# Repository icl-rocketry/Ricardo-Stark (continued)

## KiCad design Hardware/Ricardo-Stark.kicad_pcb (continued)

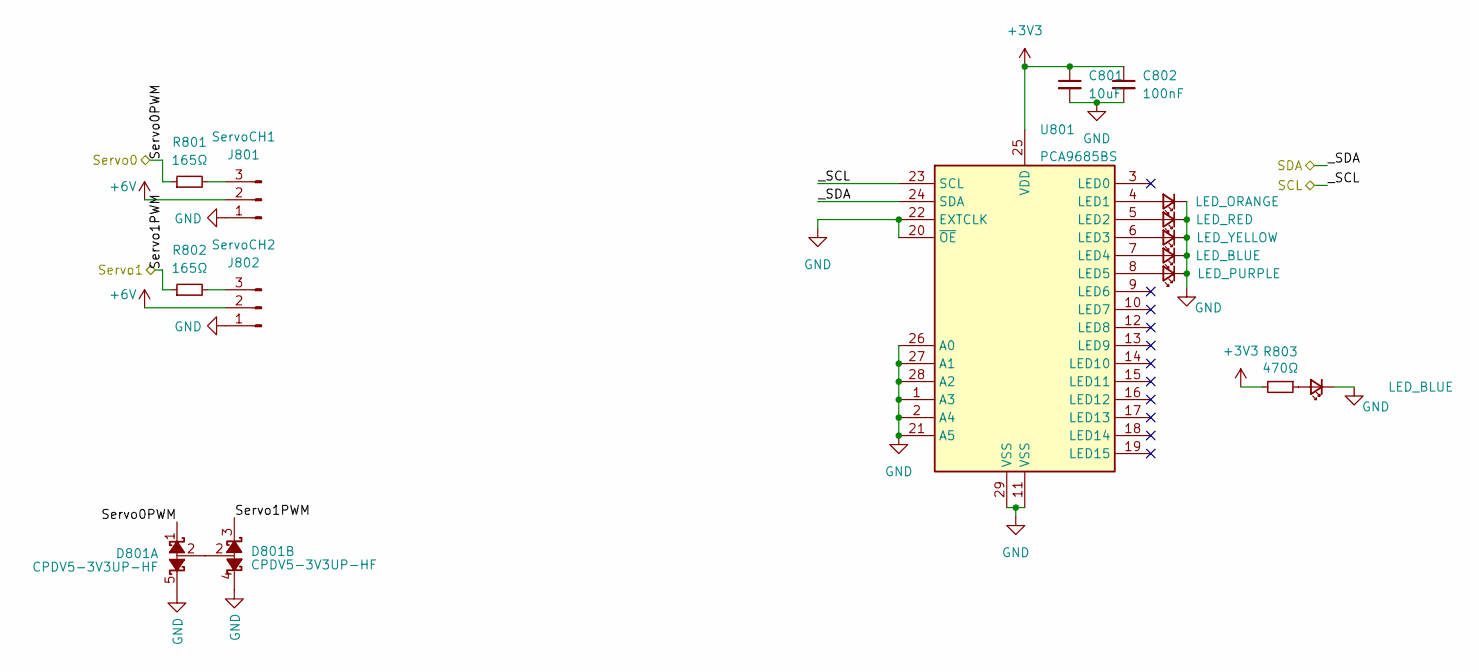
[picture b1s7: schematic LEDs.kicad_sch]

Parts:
C801: 10uF; C_0402_1005Metric
C802: 100nF; C_0402_1005Metric
D801: CPDV5-3V3UP-HF; SOT-353_SC-70-5
D802: LED_ORANGE; LED_0402_1005Metric
D803: LED_RED; LED_0402_1005Metric
D804: LED_YELLOW; LED_0402_1005Metric
D805, D807: LED_BLUE; LED_0402_1005Metric
D806: LED_PURPLE; LED_0402_1005Metric
J801: ServoCH1; Molex_Nano-Fit_105313-xx03_1x03_P2.50mm_Horizontal
J802: ServoCH2; Molex_Nano-Fit_105313-xx03_1x03_P2.50mm_Horizontal
R801, R802: 165Ω; R_0402_1005Metric
R803: 470Ω; R_0402_1005Metric
U801: PCA9685BS; QFN-28-1EP_6x6mm_P0.65mm_EP4.25x4.25mm

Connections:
+3.3V: C801.1, C802.1, R803.2, U801.25 (VDD); also elsewhere on the board
+6V: J801.2, J802.2; also elsewhere on the board
/SCL: U801.23 (SCL); also elsewhere on the board
/SDA: U801.24 (SDA); also elsewhere on the board
/Servo0: D801.1, R801.1; also elsewhere on the board
/Servo1: D801.3, R802.1; also elsewhere on the board
GND: C801.2, C802.2, D801.4, D801.5, D802.1 (K), D803.1 (K), D804.1 (K), D805.1 (K), D806.1 (K), D807.1 (K), J801.1, J802.1, U801.1 (A3), U801.2 (A4), U801.11 (VSS), U801.20 (~OE), U801.21 (A5), U801.22 (EXTCLK), U801.26 (A0), U801.27 (A1), U801.28 (A2), U801.29 (VSS); also elsewhere on the board
unnamed: D802.2 (A), U801.4 (LED1)
unnamed: D803.2 (A), U801.5 (LED2)
unnamed: D804.2 (A), U801.6 (LED3)
unnamed: D805.2 (A), U801.7 (LED4)
unnamed: D806.2 (A), U801.8 (LED5)
unnamed: D807.2 (A), R803.1
unnamed: J801.3, R801.2
unnamed: J802.3, R802.2

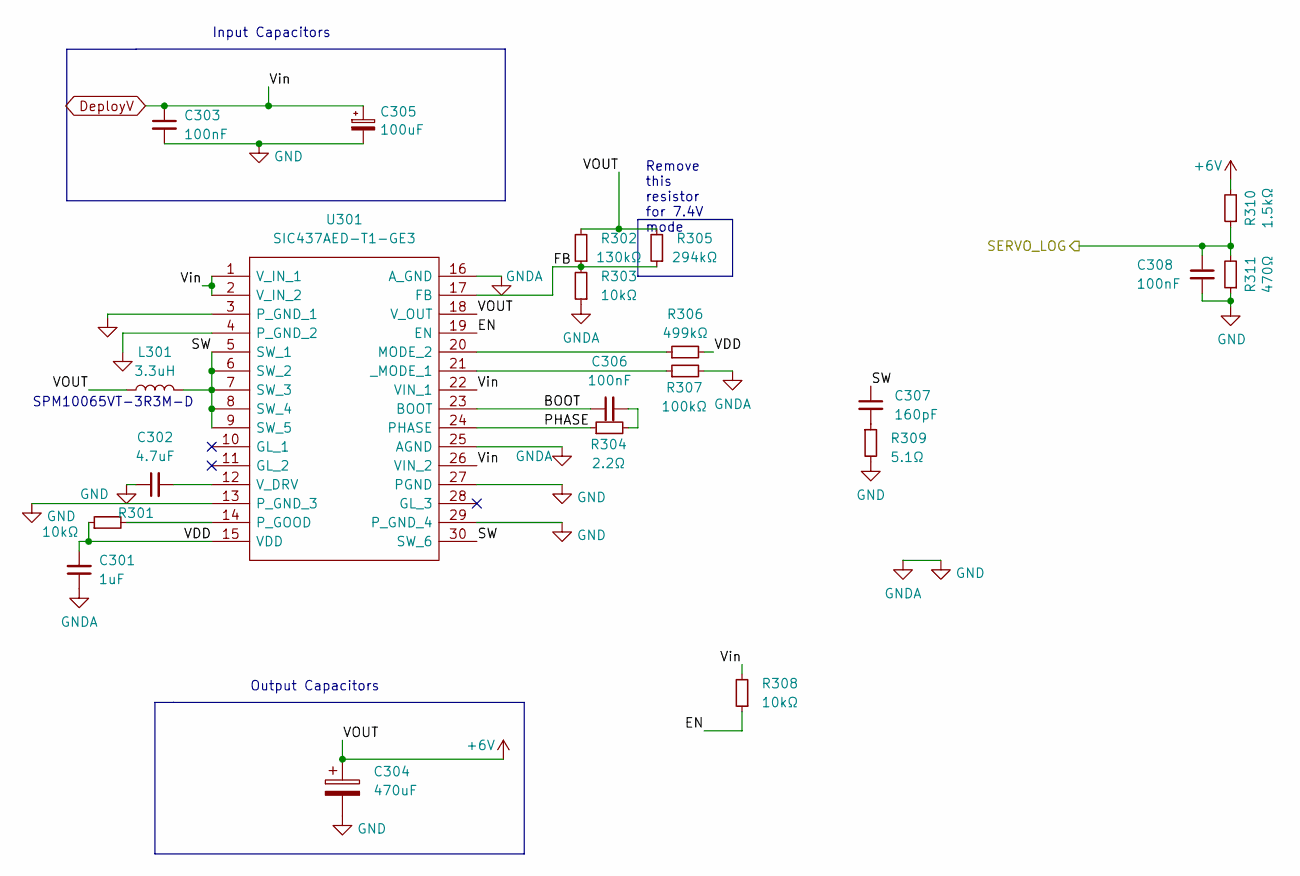
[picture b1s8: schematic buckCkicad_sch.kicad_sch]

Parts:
C301: 1uF; C_0402_1005Metric
C302: 4.7uF; C_0402_1005Metric
C303, C306, C308: 100nF; C_0402_1005Metric
C304: 470uF; CP_Elec_6.3x7.7
C305: 100uF; CP_EIA-7360-38_Kemet-E
C307: 160pF; C_0603_1608Metric
L301: 3.3uH; IND_SPM10065VT-3R3M-D
R301, R303, R308: 10kΩ; R_0402_1005Metric
R302: 130kΩ; R_0402_1005Metric
R304: 2.2Ω; R_0402_1005Metric
R305: 294kΩ; R_0603_1608Metric_Pad0.98x0.95mm_HandSolder
R306: 499kΩ; R_0402_1005Metric
R307: 100kΩ; R_0402_1005Metric
R309: 5.1Ω; R_0603_1608Metric
R310: 1.5kΩ; R_0402_1005Metric
R311: 470Ω; R_0402_1005Metric
U301: SIC437AED-T1-GE3; SiC437BEDT1GE3; Manufacturer_Part_Number SiC437BED-T1-GE3; Mouser Part Number 78-SIC437BED-T1-GE3

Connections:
+6V: C304.1, L301.1, R302.2, R305.2, R310.2, U301.18 (V_OUT); also elsewhere on the board
/ServoPower/BOOT: C306.1, U301.23 (BOOT)
/ServoPower/EN: R308.1, U301.19 (EN)
/ServoPower/FB: R302.1, R303.2, R305.1, U301.17 (FB)
/ServoPower/PHASE: R304.1, U301.24 (PHASE)
/ServoPower/SW: C307.1, L301.2, U301.5 (SW_1), U301.6 (SW_2), U301.7 (SW_3), U301.8 (SW_4), U301.9 (SW_5), U301.30 (SW_6)
/ServoPower/VDD: C301.2, R301.1, R306.2, U301.15 (VDD)
/ServoV_LOG: C308.1, R310.1, R311.2; also elsewhere on the board
DeployV: C303.1, C305.1, R308.2, U301.1 (V_IN_1), U301.2 (V_IN_2), U301.22 (VIN_1), U301.26 (VIN_2); also elsewhere on the board
GND: C301.1, C302.1, C303.2, C304.2, C305.2, C308.2, R303.1, R307.2, R309.2, R311.1, U301.3 (P_GND_1), U301.4 (P_GND_2), U301.13 (P_GND_3), U301.16 (A_GND), U301.25 (AGND), U301.27 (PGND), U301.29 (P_GND_4); also elsewhere on the board
unnamed: C306.2, R304.2
unnamed: C307.2, R309.1
unnamed: R306.1, U301.20 (MODE_2)
unnamed: R301.2, U301.14 (P_GOOD)
unnamed: C302.2, U301.12 (V_DRV)
unnamed: R307.1, U301.21 (_MODE_1)

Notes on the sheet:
SPM10065VT-3R3M-D
Input Capacitors
Output Capacitors
Remove this resistor for 7.4V mode

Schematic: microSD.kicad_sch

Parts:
C1001: 100nF; C_0402_1005Metric
J1001: Conn_01x07_Socket; Molex_Pico-Clasp_202396-0707_1x07-1MP_P1.00mm_Horizontal
J1002: ST1W008S4TR2000; JAE_ST1W008S4TR2000; PARTREV 1
R1001, R1002: 10kΩ; R_0402_1005Metric

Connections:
+3.3V: C1001.1, J1001.7, J1002.C4, R1001.1, R1002.2; also elsewhere on the board
/SD1_CS: J1002.C2; also elsewhere on the board
/SD1_DET: J1002.SW, R1002.1; also elsewhere on the board
/SD2_CS: J1001.2; also elsewhere on the board
/SD2_DET: J1001.1, R1001.2; also elsewhere on the board
/VSPI_MISO: J1001.6, J1002.C7; also elsewhere on the board
/VSPI_MOSI: J1001.3, J1002.C3; also elsewhere on the board
/VSPI_SCLK: J1001.5, J1002.C5; also elsewhere on the board
GND: C1001.2, J1001.4, J1002.C6, J1002.GND1 (GND), J1002.GND2 (GND), J1002.GND3 (GND), J1002.GND4 (GND); also elsewhere on the board

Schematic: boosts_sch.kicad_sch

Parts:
C401, C422: 10uF; C_0402_1005Metric
C402, C409, C411, C420, C421, C423: 100nF; C_0402_1005Metric
C403: 2.2uF; C_0603_1608Metric
C404: 180pF; C_0402_1005Metric
C405: 3.9nF; C_0402_1005Metric
C406, C413: 1uF; C_0402_1005Metric
C407, C408, C417, C419: 22uF; C_0805_2012Metric
C410, C418: 2.2uF; C_0402_1005Metric
C412: 47uF; C_1206_3216Metric
C414: 10uF; C_0603_1608Metric
C415: 120pF; C_0402_1005Metric
C416: 2.2nF; C_0402_1005Metric
C424: 22uF; C_1206_3216Metric
L401, L402: 5uH; IND_SRP6540-390M; Manufacturer_Part_Number SRR6038-5R0Y; Mouser Part Number 652-SRR6038-5R0Y
R401: 7.87kΩ; R_0402_1005Metric
R402: 360kΩ; R_0402_1005Metric
R403, R411: 100kΩ; R_0402_1005Metric
R404, R414: 10kΩ; R_0402_1005Metric
R405: 560kΩ; R_0402_1005Metric
R406, R412: 49.9kΩ; R_0402_1005Metric
R407: 150kΩ; R_0402_1005Metric
R408: 301kΩ; R_0402_1005Metric
R409: 18.7kΩ; R_0402_1005Metric
R410: 976kΩ; R_0402_1005Metric
R413: 432kΩ; R_0402_1005Metric
R415: 475kΩ; R_0402_1005Metric
R416: 287kΩ; R_0402_1005Metric
U401, U404: TPS61089RNRR; IC_TPS61089RNRR; Manufacturer_Part_Number TPS61089RNRR; Mouser Part Number 595-TPS61089RNRR
U402, U403: AP2205-W5-7; SOT95P282X145-5N; Mouser Part Number 621-AP2205-W5-7

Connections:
+3.3V: C411.1, C412.1, C421.1, C424.1, L401.1, L402.1, R404.2, R414.2, U401.9 (VIN), U404.9 (VIN); also elsewhere on the board
+5V: C410.1, R407.2, U402.5 (VOUT); also elsewhere on the board
+12V: C418.1, R413.2, U403.5 (VOUT); also elsewhere on the board
/Boosts/FB_5V: R402.1, R403.2, U401.3 (FB)
/Boosts/FB_12V: R410.1, R411.2, U404.3 (FB)
/Boosts/LDO5.5V_IN: C401.1, C402.1, C406.1, C407.1, C408.1, R402.2, U401.6 (VOUT), U402.1 (VIN), U402.3 (EN)
/Boosts/LDO12V_IN: C413.1, C417.1, C419.1, C422.1, C423.1, R410.2, U403.1 (VIN), U403.3 (EN), U404.6 (VOUT)
/Boosts/SW_5V: R408.1, U401.1 (FSW)
/Boosts/SW_12V: R416.1, U404.1 (FSW)
GND: C401.2, C402.2, C403.2, C404.2, C405.2, C406.2, C407.2, C408.2, C410.2, C411.2, C412.2, C413.2, C414.2, C415.2, C416.2, C417.2, C418.2, C419.2, C421.2, C422.2, C423.2, C424.2, R403.1, R405.1, R406.1, R411.1, R412.1, R415.1, U401.5 (GND), U402.2 (GND), U403.2 (GND), U404.5 (GND); also elsewhere on the board
unnamed: C405.1, R401.2
unnamed: C416.1, R409.2
unnamed: C409.1, U401.10 (BOOT)
unnamed: C404.1, R401.1, U401.4 (COMP)
unnamed: R404.1, U401.7 (EN)
unnamed: R405.2, U401.8 (ILIM)
unnamed: C409.2, L401.2, R408.2, U401.11 (SW)
unnamed: C403.1, U401.2 (VCC)
unnamed: R406.2, R407.1, U402.4 (ADJ/NC)
unnamed: R412.2, R413.1, U403.4 (ADJ/NC)
unnamed: C420.1, U404.10 (BOOT)
unnamed: C415.1, R409.1, U404.4 (COMP)
unnamed: R414.1, U404.7 (EN)
unnamed: R415.2, U404.8 (ILIM)
unnamed: C420.2, L402.2, R416.2, U404.11 (SW)
unnamed: C414.1, U404.2 (VCC)

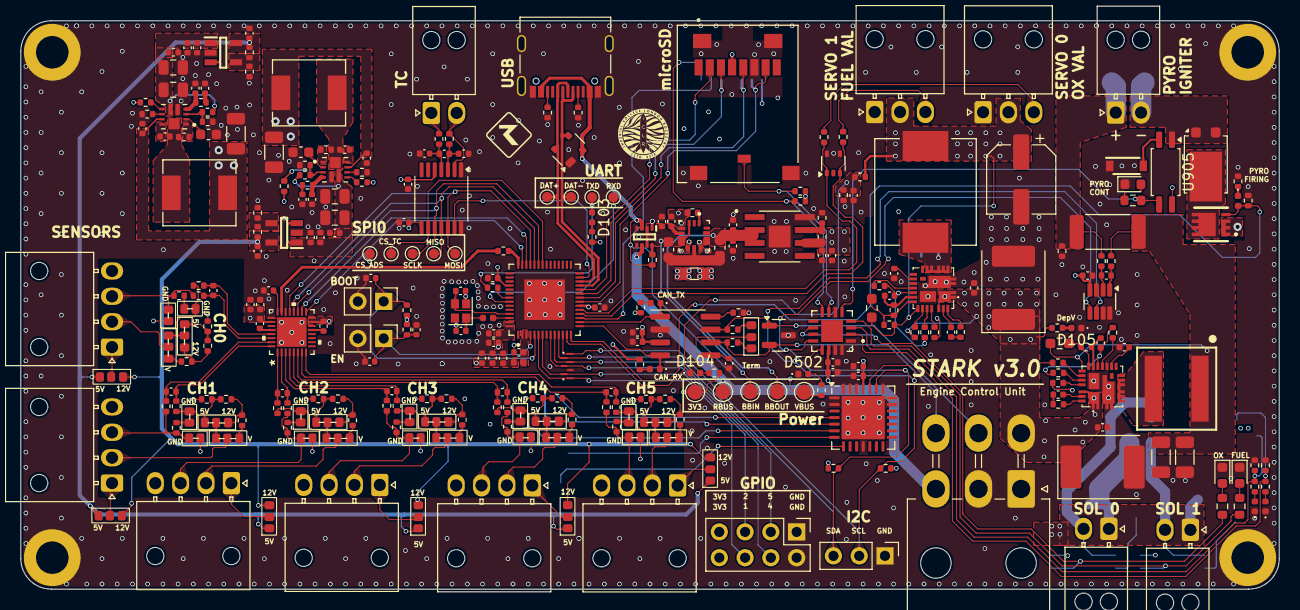
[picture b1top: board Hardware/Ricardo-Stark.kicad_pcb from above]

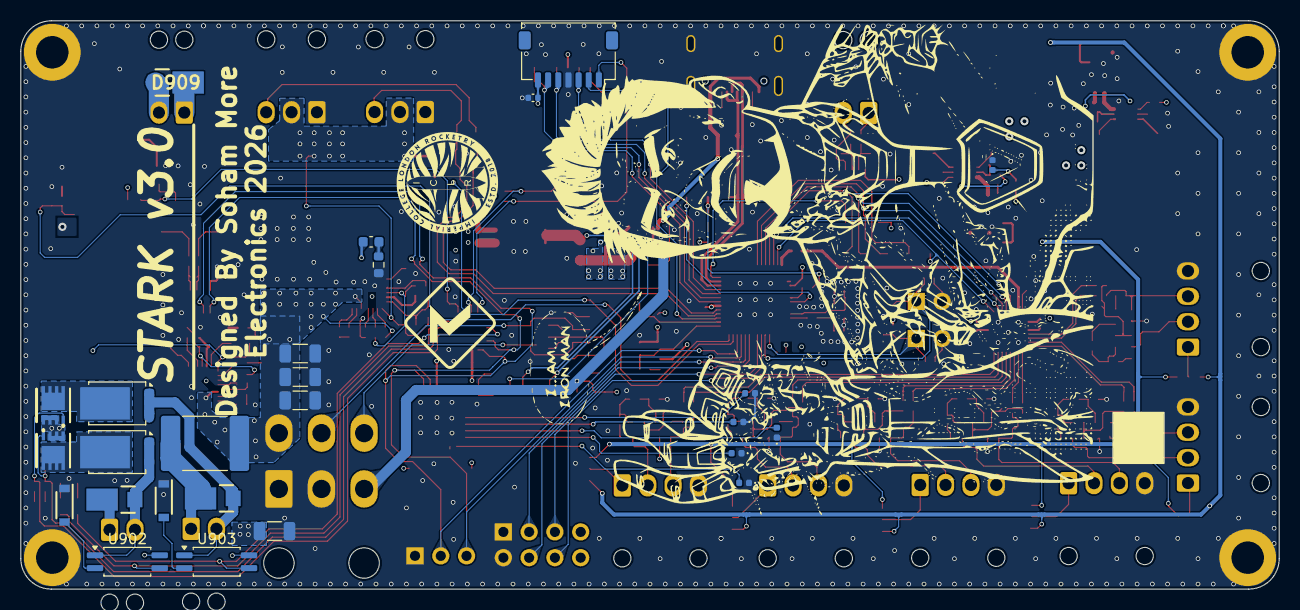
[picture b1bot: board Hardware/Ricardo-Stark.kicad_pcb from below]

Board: 4 copper layers, 124.0 x 56.0 mm, 332 parts (26 on the bottom side), 212 nets.

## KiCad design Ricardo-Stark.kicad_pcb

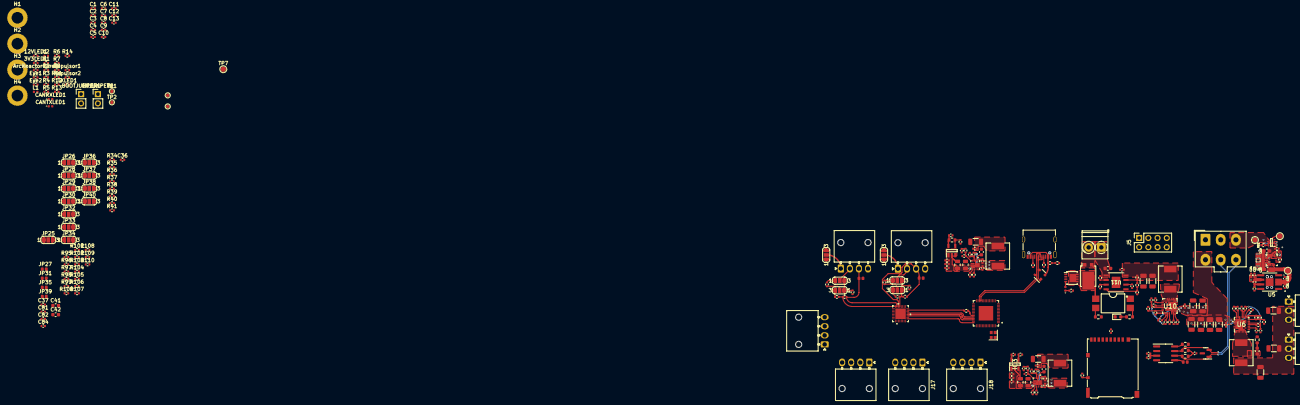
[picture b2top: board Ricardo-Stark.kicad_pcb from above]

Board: 4 copper layers, 265 parts (0 on the bottom side), 164 nets.

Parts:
3V3LED1: BLUE_LED; R_0402_1005Metric
12VLED1: RED_LED; R_0402_1005Metric
ArcReactorCore1: Blue_LED; R_0402_1005Metric
BOOTJUMPER1: Conn_01x02_Male; PinHeader_1x02_P2.54mm_Vertical
C1, C15, C17, C21, C23, C58, C68: 10uF; C_0402_1005Metric
C2, C4, C7, C19, C25, C37, C51, C60, C73, C82: 1uF; C_0402_1005Metric
C3, C5, C6, C8, C10, C11, C24, C35, C36, C76, C77, C84: 0.1uF; C_0402_1005Metric
C9: 10nF; C_0402_1005Metric
C12, C13: 11pF; C_0402_1005Metric
C14, C34, C54, C56, C59, C66, C67, C69, C83, C86: 100nF; C_0402_1005Metric
C16: 47nF; C_0402_1005Metric
C18, C41, C61: 10uF; C_0603_1608Metric
C20: 22uF; C_0603_1608Metric
C22, C26, C74: 4.7uF; C_0402_1005Metric
C27, C28, C40, C57, C75, C80, C85: 47uF; C_1206_3216Metric
C29: 68uF; C_1206_3216Metric
C30, C32: DNP; C_1206_3216Metric
C31, C33: 220uF; C_1206_3216Metric
C39, C52, C53, C64: 22uF; C_0805_2012Metric
C42: 100nF; C_0603_1608Metric
C48: 2.2uF; C_0603_1608Metric
C49: 180pF; C_0402_1005Metric
C50: 3.9nF; C_0402_1005Metric
C55, C65: 2.2uF; C_0402_1005Metric
C62: 120pF; C_0402_1005Metric
C63, C87: 2.2nF; C_0402_1005Metric
C70: 22uF; C_1206_3216Metric
C78: 680pF; C_0603_1608Metric
C81: 220nF; C_0402_1005Metric
C88: 1uF; C_0603_1608Metric
CANRXLED1: CANRXLED; LED_0402_1005Metric
CANTXLED1: CANTXLED; LED_0402_1005Metric
D1: SM712_SOT23; SOT-23
D2: SP0503BAHT; SOT-143
D3: DST1550S; TO-277B
D4: RED_LED; LED_0603_1608Metric
ENJUMPER1: Conn_01x02_Male; PinHeader_1x02_P2.54mm_Vertical
Eye1, Eye2: Blue_LED; R_0402_1005Metric
Firing1: EMERALD_LED; LED_0402_1005Metric
H1, H2, H3, H4: MountingHole_Pad; MountingHole_3.2mm_M3_DIN965_Pad
IC1, IC4: TPS61089RNRR; IC_TPS61089RNRR
IC2, IC3: AP2205-W5-7; SOT95P282X145-5N
J1: RBUS; Molex_Mini-Fit_Jr_5566-06A_2x03_P4.20mm_Vertical
J2: USB_C_Receptacle_USB2.0; USB_C_Receptacle_Palconn_UTC16-G
J3: ServoCH1; Molex_Nano-Fit_105313-xx03_1x03_P2.50mm_Horizontal
J4: ServoCH2; Molex_Nano-Fit_105313-xx03_1x03_P2.50mm_Horizontal
J5: GPIO Breakout; PinSocket_2x04_P2.54mm_Vertical
J7, J14, J15, J16, J17, J18: 1053131104; Molex_Nano-Fit_105313-xx04_1x04_P2.50mm_Horizontal
J12: Conn_01x02_Male; TerminalBlock_Phoenix_PT-1,5-2-3.5-H_1x02_P3.50mm_Horizontal
J13: Micro_SD_Card_Det; microSD_HC_Hirose_DM3AT-SF-PEJM5
JP1: TermJP; SmallerSolderJP
JP5, JP10, JP20, JP21, JP22, JP24, JP25, JP26, JP28, JP29, JP30, JP32, JP33, JP34, JP36, JP37, JP38, JP40: SolderJumper_3_Open; SolderJumper-3_P1.3mm_Open_RoundedPad1.0x1.5mm_NumberLabels
JP8, JP23, JP27, JP31, JP35, JP39: SolderJumper_2_Open; SmallerSolderJP
L1: 2.0nH; L_0402_1005Metric
L2: 20nH; L_0402_1005Metric
L3: 1uH; L_0805_2012Metric
L4, L7: 3.3uH; IND_SRP6540-390M
L5, L6: SRR6038-5R0Y; IND_SRP6540-390M
Q2: BUK9M11-40EX; LFPAK33
R1, R5, R9, R10: 10K; R_0402_1005Metric
R2, R3, R11, R12, R13: 1k; R_0402_1005Metric
R4, R6, R35: 470; R_0402_1005Metric
R7: 499R; R_0402_1005Metric
R8, R14: 3k; R_0402_1005Metric
R15: 0; R_0603_1608Metric
R16, R17: 60; R_0603_1608Metric
R18, R19, R20: 5.1k; R_0402_1005Metric
R21, R24, R25, R27, R33, R48, R76, R81, R83, R88, R89, R96, R100, R104, R108: 10k; R_0402_1005Metric
R22: 14k; R_0402_1005Metric
R23: 56k; R_0402_1005Metric
R26: 130k; R_0402_1005Metric
R28, R84: 2.2; R_0402_1005Metric
R29: 294k; R_0402_1005Metric
R30: 464K; R_0402_1005Metric
R31, R86: 200k; R_0402_1005Metric
R32, R62, R69, R87: 100k; R_0402_1005Metric
R34: 1.5k; R_0402_1005Metric
R36, R37, R38, R39, R40, R41: DNP; R_0402_1005Metric
R45, R75, R95, R99, R103, R107: 58.4k; R_0402_1005Metric
R51, R92, R98, R102, R106, R110: 49; R_0402_1005Metric
R60: 7.87k; R_0402_1005Metric
R61: 360k; R_0402_1005Metric
R63: 560k; R_0402_1005Metric
R64: 50k; R_0402_1005Metric
R65: 152k; R_0603_1608Metric
R66: 301k; R_0402_1005Metric
R67: 18.7k; R_0402_1005Metric
R68: 900k; R_0402_1005Metric
R70: 51k; R_0402_1005Metric
R71: 33.2k; R_0402_1005Metric
R72: 475k; R_0402_1005Metric
R73: 287k; R_0402_1005Metric
R74, R78, R97, R101, R105, R109: 31.6k; R_0402_1005Metric
R77: 120; R_0402_1005Metric
R79: 120; R_0603_1608Metric
R80: 10k; R_0603_1608Metric
R82: 190k; R_0402_1005Metric
R85: 47.5k; R_0402_1005Metric
R90: 5.1; R_0603_1608Metric
R91: 54.9R; R_0402_1005Metric
R93: 453; R_0402_1005Metric
R94: 11.52; R_0402_1005Metric
Repulsor1, Repulsor2: White_LED; R_0402_1005Metric
TP1, TP2, TP3, TP4: TestPoint; TestPoint_Pad_D1.0mm
TP5, TP6, TP7, TP8: TestPoint; TestPoint_Pad_D1.5mm
TXLED1: GREEN_LED; R_0402_1005Metric
U1: ESP32-S3; QFN40P700X700X90-57N
U2: SN65HVD230; SOIC-8_3.9x4.9mm_P1.27mm
U3: LM66200DRLR; SOTFL50P160X60-8N
U4: MAX77827AEFD+T; CONV_MAX77827AEFD+T
U5: SC4215; SOIC127P599X175-9N
U6, U10: SiC437BED-T1-GE3; SiC437BEDT1GE3
U7: ADS131M06IPBS; ADS131M06IRSNR
U9: 859-LTV-247; SMDIP-4_W9.53mm
U11: TPS259621DDAT; SO-PP-DDA-8_TEX
USBLED1: WHITE_LED; R_0402_1005Metric
Y1: R940000171; Crystal_SMD_2016-4Pin_2.0x1.6mm

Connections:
+3.3V: C1.1, C4.1, C5.1, C7.1, C9.1, C10.1, C11.1, C14.1, C15.1, C23.2, C24.2, C37.1, C41.1, C42.1, C56.1, C57.1, C67.1, C70.1, C77.1, C82.1, C84.1, IC1.9 (VIN), IC4.9 (VIN), J5.5, J13.4 (VDD), L1.1, L5.1, L6.1, R1.1, R2.1, R3.1, R4.1, R5.1, R6.2, R9.2, R10.2, R11.1, R12.1, R13.1, R14.1, R23.1, R36.1, R37.1, R38.1, R39.1, R40.1, R41.1, R89.1, R94.2, TP7.1, U1.20 (VDD3P3_RTC), U1.46 (VDD3P3_CPU), U1.55 (VDDA), U1.56 (VDDA), U2.3 (VCC), U5.6 (VOUT), U7.15 (AVDD), U7.16 (SYNC/RESET), U7.26 (DVDD), U9.16
+5V: C55.1, IC2.5 (VOUT), JP10.1 (A), JP24.1 (A), JP28.1 (A), JP32.1 (A), JP36.1 (A), JP40.1 (A), R65.2
+6V: C29.1, C31.1, C33.1, C36.1, J3.2, J4.2, L4.1, R26.2, R29.2, R34.2, U6.18 (V_OUT)
+12V: C65.1, IC3.5 (VOUT), JP10.3 (B), JP24.3 (B), JP28.3 (B), JP32.3 (B), JP36.3 (B), JP40.3 (B)
/ADS_CLK: R91.1, U7.23 (XTAL1/CLKIN)
/ADS_CS0: U1.42 (GPIO37), U7.17 (CS)
/BOOT: BOOTJUMPER1.1, C8.1, R5.2, U1.5 (GPIO0/BOOT)
/Boosts/FB_5V: IC1.3 (FB), R61.1, R62.2
/Boosts/FB_12V: IC4.3 (FB), R68.1, R69.2
/Boosts/LDO5.5V_IN: C51.1, C52.1, C53.1, C58.1, C59.1, IC1.6 (VOUT), IC2.1 (VIN), IC2.3 (EN), R61.2
/Boosts/LDO12V_IN: C39.1, C60.1, C64.1, C68.1, C69.1, IC3.1 (VIN), IC3.3 (EN), IC4.6 (VOUT), R68.2
/Boosts/SW_5V: IC1.1 (FSW), R66.1
/Boosts/SW_12V: IC4.1 (FSW), R73.1
/CAN+: D1.2 (A2), J1.5, R16.1, U2.7 (CANH)
/CAN-: D1.1 (A1), J1.6, R17.2, U2.6 (CANL)
/CAN-BUS/Vref: JP1.1 (A), U2.5 (Vref)
/CAN_RX: CANRXLED1.1 (K), U1.6 (GPIO1/ADC1_CH0), U2.4 (R)
/CAN_TX: CANTXLED1.1 (K), U1.7 (GPIO2/ADC1_CH1), U2.1 (D)
/CHIP_PU: C2.1, C3.1, ENJUMPER1.1, R1.2, U1.4 (CHIP_PU/RESET)
/Cont 1: R79.1, U1.28 (SPI_CS1/GPIO26), U9.15
/Data+: D2.4 (K), J2.A6 (D+), J2.B6 (D+), TP4.1, U1.26 (GPIO20/USB_D+/ADC2_CH9)
/Data-: D2.3 (K), J2.A7 (D-), J2.B7 (D-), TP3.1, U1.25 (GPIO19/USB_D-/ADC2_CH8)
/HSPI_MISO: U1.39 (GPIO34), U7.20 (DOUT)
/HSPI_MOSI: U1.38 (GPIO33), U7.21 (DIN)
/HSPI_SCLK: U1.40 (GPIO35), U7.19 (SCLK)
/Nuke 1: Firing1.2 (A), Q2.4 (G), U1.27 (GPIO21)
/Power/BBIN: C17.1, C18.1, TP5.1, U3.2 (VOUT_1), U3.7 (VOUT_2), U4.3 (EN), U4.6 (IN)
/Power/BBOUT: C20.1, C21.1, C22.1, TP8.1, U4.11 (OUT), U4.13 (OUTS), U5.2 (EN), U5.3 (VIN)
/Power/BIAS: C19.1, U4.5 (BIAS)
/Power/FBIn: R23.2, R24.1, U5.7 (ADJ)
/Power/LX1: L3.1, U4.8 (LX1)
/Power/LX2: L3.2, U4.10 (LX2)
/Power/SEL: R22.1, U4.1 (SEL)
/Pyro/BOOT: C76.1, U10.23 (BOOT)
/Pyro/EFuse_In: C40.1, C75.1, C86.1, L7.1, R30.2, R82.2, U10.18 (V_OUT), U11.4 (IN)
/Pyro/EN: R88.1, U10.19 (EN)
/Pyro/FB: R82.1, R83.2, U10.17 (FB)
/Pyro/PHASE: R84.1, U10.24 (PHASE)
/Pyro/PyroV: C88.2, J12.1, U11.5 (OUT)
/Pyro/SW: L7.2, U10.5 (SW_1), U10.6 (SW_2), U10.7 (SW_3), U10.8 (SW_4), U10.9 (SW_5), U10.30 (SW_6)
/Pyro/VDD: C73.2, R81.1, R86.2, U10.15 (VDD)
/Pyro_IMON: R93.1, U1.24 (GPIO18/ADC2_CH7/DAC_1), U11.7 (ILM)
/RXD: TP2.1, U1.50 (U0RXD/PROG/GPIO44)
/SD1_DET: J13.10 (DET_A), R89.2, U1.23 (GPIO17/ADC2_CH6/DAC_2)
/Servo1PWM: J3.3, U1.16 (GPIO11/ADC2_CH0)
/Servo2PWM: J4.3, U1.15 (GPIO10/ADC1_CH9)
/ServoV_LOG: C36.2, R34.1, R35.2, U1.18 (GPIO13/ADC2_CH2)
/TXD: R7.1, TP1.1, TXLED1.1 (K)
/actuators/GPIO0: J5.2, R36.2
/actuators/GPIO1: J5.3, R37.2
/actuators/GPIO2: J5.4, R38.2
/actuators/GPIO3: J5.6, R39.2
/actuators/GPIO4: J5.7, R40.2
/actuators/GPIO5: J5.8, R41.2
/buckC/BOOT: C35.1, U6.23 (BOOT)
/buckC/EN: R33.1, U6.19 (EN)
/buckC/FB: R26.1, R27.2, R29.1, U6.17 (FB)
/buckC/PHASE: R28.1, U6.24 (PHASE)
/buckC/SW: C78.1, L4.2, U6.5 (SW_1), U6.6 (SW_2), U6.7 (SW_3), U6.8 (SW_4), U6.9 (SW_5), U6.30 (SW_6)
/buckC/VDD: C25.2, R25.1, R31.2, U6.15 (VDD)
/pressure_sensor/AIN0N: J7.3, JP8.2 (B), R51.2, U7.30 (AIM0N)
/pressure_sensor/AIN0P: JP5.3 (B), JP20.1 (A), R51.1, R75.2, R76.2, U7.29 (AIN0P)
/pressure_sensor/AIN1N: J14.3, JP23.2 (B), R92.2, U7.31 (AIN1N)
/pressure_sensor/AIN1P: JP21.3 (B), JP22.1 (A), R45.2, R48.2, R92.1, U7.32 (AIN1P)
/pressure_sensor/AIN2N: J15.3, JP27.2 (B), R98.2, U7.2 (AIN2N)
/pressure_sensor/AIN2P: JP25.3 (B), JP26.1 (A), R95.2, R96.2, R98.1, U7.1 (AIN2P)
/pressure_sensor/AIN3N: J16.3, JP31.2 (B), R102.2, U7.3 (AIN3N)
/pressure_sensor/AIN3P: JP29.3 (B), JP30.1 (A), R99.2, R100.2, R102.1, U7.4 (AIN3P)
/pressure_sensor/AIN4N: J17.3, JP35.2 (B), R106.2, U7.6 (AIN4N)
/pressure_sensor/AIN4P: JP33.3 (B), JP34.1 (A), R103.2, R104.2, R106.1, U7.5 (AIN4P)
/pressure_sensor/AIN5N: J18.3, JP39.2 (B), R110.2, U7.7 (AIN5N)
/pressure_sensor/AIN5P: JP37.3 (B), JP38.1 (A), R107.2, R108.2, R110.1, U7.8 (AIN5P)
DeployV: C27.1, C28.1, C30.1, C32.1, C34.1, C80.1, C83.1, C85.1, J1.4, R8.1, R33.2, R88.2, U6.1 (V_IN_1), U6.2 (V_IN_2), U6.22 (VIN_1), U6.26 (VIN_2), U10.1 (V_IN_1), U10.2 (V_IN_2), U10.22 (VIN_1), U10.26 (VIN_2)
GND: 3V3LED1.1 (K), 12VLED1.1 (K), ArcReactorCore1.1 (K), BOOTJUMPER1.2, C1.2, C2.2, C3.2, C4.2, C5.2, C6.2, C7.2, C8.2, C9.2, C10.2, C11.2, C12.2, C13.2, C14.2, C15.2, C16.2, C17.2, C18.2, C19.2, C20.2, C21.2, C22.2, C23.1, C24.1, C25.1, C26.1, C27.2, C28.2, C29.2, C30.2, C31.2, C32.2, C33.2, C34.2, C37.2, C39.2, C40.2, C41.2, C42.2, C48.2, C49.2, C50.2, C51.2, C52.2, C53.2, C55.2, C56.2, C57.2, C58.2, C59.2, C60.2, C61.2, C62.2, C63.2, C64.2, C65.2, C67.2, C68.2, C69.2, C70.2, C73.1, C74.1, C75.2, C77.2, C80.2, C81.2, C82.2, C83.2, C84.2, C85.2, C86.2, C87.1, C88.1, D1.3 (common), D2.1 (A), D4.1 (K), ENJUMPER1.2, Eye1.1 (K), Eye2.1 (K), H1.1, H2.1, H3.1, H4.1, IC1.5 (GND), IC2.2 (GND), IC3.2 (GND), IC4.5 (GND), J1.1, J1.2, J2.A1 (GND), J2.A12 (GND), J2.B1 (GND), J2.B12 (GND), J2.S1 (SHIELD), J3.1, J4.1, J5.1, J7.4, J13.6 (VSS), J13.9 (DET_B), J13.11 (SHIELD), J14.4, J15.4, J16.4, J17.4, J18.4, JP8.1 (A), JP23.1 (A), JP27.1 (A), JP31.1 (A), JP35.1 (A), JP39.1 (A), Q2.1 (S), Q2.2 (S), Q2.3 (S), R15.2, R18.2, R19.1, R22.2, R24.2, R27.1, R32.2, R35.1, R48.1, R62.1, R63.1, R64.1, R69.1, R70.1, R72.1, R76.1, R77.2, R80.2, R83.1, R85.2, R87.2, R90.2, R93.2, R96.1, R100.1, R104.1, R108.1, Repulsor1.1 (K), Repulsor2.1 (K), U1.57 (GND), U2.2 (GND), U3.1 (GND_1), U3.4 (~ON), U3.5 (GND_2), U4.4 (AGND), U4.9 (PGND), U5.8 (GND), U5.9 (GND), U6.3 (P_GND_1), U6.4 (P_GND_2), U6.13 (P_GND_3), U6.16 (A_GND), U6.25 (AGND), U6.27 (PGND), U6.29 (P_GND_4), U7.13 (AGND), U7.22 (XTAL2), U7.25 (DGND), U7.28 (AGND), U10.3 (P_GND_1), U10.4 (P_GND_2), U10.13 (P_GND_3), U10.16 (A_GND), U10.25 (AGND), U10.27 (PGND), U10.29 (P_GND_4), U11.1 (GND), U11.EPAD (GND), USBLED1.1 (K), Y1.2, Y1.4
unnamed: 3V3LED1.2 (A), R6.1
unnamed: 12VLED1.2 (A), R8.2
unnamed: ArcReactorCore1.2 (A), R11.2
unnamed: C6.1, L1.2, U1.2 (VDD3P3), U1.3 (VDD3P3)
unnamed: C13.1, L2.2, Y1.1
unnamed: C35.2, R28.2
unnamed: C50.1, R60.2
unnamed: C63.1, R67.2
unnamed: C76.2, R84.2
unnamed: C78.2, R90.1
unnamed: CANRXLED1.2 (A), R3.2
unnamed: CANTXLED1.2 (A), R2.2
unnamed: D3.3 (K), Q2.5 (D)
unnamed: D4.2 (A), R79.2
unnamed: Eye1.2 (A), Eye2.2 (A), R14.2
unnamed: Firing1.1 (K), R77.1
unnamed: C54.1, IC1.10 (BOOT)
unnamed: C49.1, IC1.4 (COMP), R60.1
unnamed: IC1.7 (EN), R9.1
unnamed: IC1.8 (ILIM), R63.2
unnamed: C54.2, IC1.11 (SW), L5.2, R66.2
unnamed: C48.1, IC1.2 (VCC)
unnamed: IC2.4 (ADJ/NC), R64.2, R65.1
unnamed: IC3.4 (ADJ/NC), R70.2
unnamed: C66.1, IC4.10 (BOOT)
unnamed: C62.1, IC4.4 (COMP), R67.1
unnamed: IC4.7 (EN), R10.1
unnamed: IC4.8 (ILIM), R72.2
unnamed: C66.2, IC4.11 (SW), L6.2, R73.2
unnamed: C61.1, IC4.2 (VCC)
unnamed: J2.A5 (CC1), R18.1
unnamed: J2.B5 (CC2), R19.2
unnamed: D3.1 (A), D3.2 (A), J12.2, U9.1
unnamed: C16.1, JP1.2 (B), R16.2, R17.1
unnamed: JP5.1 (A), R74.1
unnamed: J7.2, JP5.2 (C)
unnamed: J7.1, JP10.2 (C)
unnamed: JP20.3 (B), R75.1
unnamed: JP20.2 (C), R74.2
unnamed: JP21.1 (A), R78.1
unnamed: J14.2, JP21.2 (C)
unnamed: JP22.3 (B), R45.1
unnamed: JP22.2 (C), R78.2
unnamed: J14.1, JP24.2 (C)
unnamed: JP25.1 (A), R97.1
unnamed: J15.2, JP25.2 (C)
unnamed: JP26.3 (B), R95.1
unnamed: JP26.2 (C), R97.2
unnamed: J15.1, JP28.2 (C)
unnamed: JP29.1 (A), R101.1
unnamed: J16.2, JP29.2 (C)
unnamed: JP30.3 (B), R99.1
unnamed: JP30.2 (C), R101.2
unnamed: J16.1, JP32.2 (C)
unnamed: JP33.1 (A), R105.1
unnamed: J17.2, JP33.2 (C)
unnamed: JP34.3 (B), R103.1
unnamed: JP34.2 (C), R105.2
unnamed: J17.1, JP36.2 (C)
unnamed: JP37.1 (A), R109.1
unnamed: J18.2, JP37.2 (C)
unnamed: JP38.3 (B), R107.1
unnamed: JP38.2 (C), R109.2
unnamed: J18.1, JP40.2 (C)
unnamed: R80.1, U9.2
unnamed: R12.2, Repulsor1.2 (A)
unnamed: R13.2, Repulsor2.2 (A)
unnamed: R4.2, TXLED1.2 (A)
unnamed: R91.2, U1.37 (SPICLK_P/GPIO47)
unnamed: R7.2, U1.49 (U0TXD/PROG/GPIO43)
unnamed: C12.1, U1.53 (XTAL_N), Y1.3
unnamed: L2.1, U1.54 (XTAL_P)
unnamed: R15.1, U2.8 (Rs)
unnamed: R21.2, U3.8 (ST)
unnamed: R31.1, U6.20 (MODE_2)
unnamed: R25.2, U6.14 (P_GOOD)
unnamed: C26.2, U6.12 (V_DRV)
unnamed: R32.1, U6.21 (_MODE_1)
unnamed: C81.1, U7.24 (CAP)
unnamed: R86.1, U10.20 (MODE_2)
unnamed: R81.2, U10.14 (P_GOOD)
unnamed: C74.2, U10.12 (V_DRV)
unnamed: R87.1, U10.21 (_MODE_1)
unnamed: R94.1, U11.6 (*FLT)
unnamed: R30.1, R71.2, U11.3 (EN/UVLO)
unnamed: R71.1, R85.1, U11.8 (OVLO/OVCSEL)
unnamed: C87.2, U11.2 (dVdt)
unnamed: R20.2, USBLED1.2 (A)
RBUS_uC_V: J1.3, TP6.1, U3.6 (VIN2)
VBUS: D2.2 (K), J2.A4 (VBUS), J2.A9 (VBUS), J2.B4 (VBUS), J2.B9 (VBUS), R20.1, R21.1, U3.3 (VIN1)

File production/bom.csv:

Designator,Footprint,Quantity,Value,LCSC Part #
"12VLED1, 3V3LED6",0402,2,RED_LED,
"3V3LED1, 3V3LED2, 3V3LED3, 3V3LED4, 3V3LED8",0402,5,BLUE_LED,
3V3LED10,0402,1,PURPLE_LED,
3V3LED5,0402,1,ORANGE_LED,
3V3LED7,0402,1,YELLOW_LED,
"3V3LED9, TXLED1",0402,2,GREEN_LED,
"BOOTJUMPER1, ENJUMPER1",PinHeader_1x02_P2.54mm_Vertical,2,Conn_01x02_Male,
"C1, C15, C17, C21, C23, C58, C68",0402,7,10uF,
"C10, C11, C24, C3, C35, C36, C5, C6, C76, C77, C8, C84",0402,12,0.1uF,
"C12, C13",0402,2,11pF,
"C14, C34, C54, C56, C59, C66, C67, C69, C83, C86",0402,10,100nF,
C16,0402,1,47nF,
"C18, C61",0603,2,10uF,
"C19, C2, C25, C37, C4, C51, C60, C7, C73, C82",0402,10,1uF,
C20,0603,1,22uF,
"C22, C26, C74",0402,3,4.7uF,
"C27, C28, C40, C57, C75, C80, C85",1206,7,47uF,
C29,CP_Elec_6.3x7.7,1,470uF,
"C30, C32",1206,2,DNP,
"C31, C33",0805,2,10uF,
"C39, C52, C53, C64",0805,4,22uF,
C48,0603,1,2.2uF,
C49,0402,1,180pF,
C50,0402,1,3.9nF,
"C55, C65",0402,2,2.2uF,
C62,0402,1,120pF,
"C63, C87",0402,2,2.2nF,
C70,1206,1,22uF,
C78,0603,1,680pF,
C81,0402,1,220nF,
C88,0603,1,1uF,
C9,0402,1,10nF,
CANRXLED1,0402,1,CANRXLED,
CANTXLED1,0402,1,CANTXLED,
D1,SOT-23,1,SM712_SOT23,
D2,SOT-143,1,SP0503BAHT,
D3,TO-277B,1,DST1550S,
D4,0603,1,RED_LED,
Firing1,0402,1,EMERALD_LED,
"H1, H2, H3, H4",MountingHole_3.2mm_M3_DIN965_Pad,4,MountingHole_Pad,
"IC1, IC4",IC_TPS61089RNRR,2,TPS61089RNRR,
"IC2, IC3",SOT95P282X145-5N,2,AP2205-W5-7,
J1,Molex_Mini-Fit_Jr_5566-06A_2x03_P4.20mm_Vertical,1,RBUS,
J12,"TerminalBlock_Phoenix_PT-1,5-2-3.5-H_1x02_P3.50mm_Horizontal",1,Conn_01x02_Male,
J13,microSD_HC_Hirose_DM3AT-SF-PEJM5,1,Micro_SD_Card_Det,
"J14, J15, J16, J17, J18, J7",Molex_Nano-Fit_105313-xx04_1x04_P2.50mm_Horizontal,6,1053131104,
J2,USB_C_Receptacle_Palconn_UTC16-G,1,USB_C_Receptacle_USB2.0,
J3,Molex_Nano-Fit_105313-xx03_1x03_P2.50mm_Horizontal,1,ServoCH1,
J4,Molex_Nano-Fit_105313-xx03_1x03_P2.50mm_Horizontal,1,ServoCH2,
J5,PinSocket_2x04_P2.54mm_Vertical,1,GPIO Breakout,
JP1,SmallerSolderJP,1,TermJP,
"JP10, JP20, JP21, JP22, JP24, JP25, JP26, JP28, JP29, JP30, JP32, JP33, JP34, JP36, JP37, JP38, JP40, JP5",SolderJumper-3_P1.3mm_Open_RoundedPad1.0x1.5mm_NumberLabels,18,SolderJumper_3_Open,
"JP2, JP23, JP27, JP3, JP31, JP35, JP39, JP8",SmallerSolderJP,8,SolderJumper_2_Open,
L1,0402,1,2.0nH,
L2,0402,1,20nH,
L3,0805,1,1uH,
"L4, L7",IND_SRP6540-390M,2,3.3uH,
"L5, L6",IND_SRP6540-390M,2,SRR6038-5R0Y,
Q1,SOT-723,1,PMOS,
Q2,LFPAK33,1,BUK9M11-40EX,
"R1, R10, R100, R104, R108, R21, R24, R25, R27, R33, R48, R5, R76, R81, R83, R88, R89, R9, R96",0402,19,10K,
"R101, R105, R109, R74, R78, R97",0402,6,31.6k,
"R102, R106, R110, R51, R92, R98",0402,6,49,
"R103, R107, R45, R75, R95, R99",0402,6,58.4k,
"R11, R12, R13, R35, R4, R44, R6",0402,7,470,
"R14, R2, R3",0402,3,1k,
R15,0603,1,0,
"R16, R17",0603,2,60,
"R18, R19, R20",0402,3,5.1k,
R22,0402,1,14k,
R23,0402,1,56k,
R26,0402,1,130k,
"R28, R84",0402,2,2.2,
R29,0402,1,294k,
R30,0402,1,464K,
"R31, R86",0402,2,200k,
"R32, R62, R69, R87",0402,4,100k,
R34,0402,1,1.5k,
"R36, R37, R38, R39, R40, R41",0402,6,DNP,
R60,0402,1,7.87k,
R61,0402,1,360k,
R63,0402,1,560k,
R64,0402,1,50k,
R65,0603,1,152k,
R66,0402,1,301k,
R67,0402,1,18.7k,
R68,0402,1,900k,
R7,0402,1,499R,
R70,0402,1,51k,
R71,0402,1,33.2k,
R72,0402,1,475k,
R73,0402,1,287k,
R77,0402,1,120,
R79,0603,1,120,
R8,0402,1,3k,
R80,0603,1,10k,
R82,0402,1,190k,
R85,0402,1,47.5k,
R90,0603,1,5.1,
R91,0402,1,54.9R,
R93,0402,1,453,
R94,0402,1,11.52,
"TP1, TP2, TP3, TP4",TestPoint_Pad_D1.0mm,4,TestPoint,
"TP5, TP6, TP7, TP8",TestPoint_Pad_D1.5mm,4,TestPoint,
U1,QFN40P700X700X90-57N,1,ESP32-S3,
"U10, U6",SiC437BEDT1GE3,2,SiC437BED-T1-GE3,
U11,SO-PP-DDA-8_TEX,1,TPS259621DDAT,
U2,SOIC-8_3.9x4.9mm_P1.27mm,1,SN65HVD230,
U3,SOTFL50P160X60-8N,1,LM66200DRLR,
U4,CONV_MAX77827AEFD+T,1,MAX77827AEFD+T,
U5,SOIC127P599X175-9N,1,SC4215,
U7,ADS131M06IRSNR,1,ADS131M06IPBS,
U9,SMDIP-4_W9.53mm,1,859-LTV-247,
USBLED1,0402,1,WHITE_LED,
Y1,Crystal_SMD_2016-4Pin_2.0x1.6mm,1,R940000171,
